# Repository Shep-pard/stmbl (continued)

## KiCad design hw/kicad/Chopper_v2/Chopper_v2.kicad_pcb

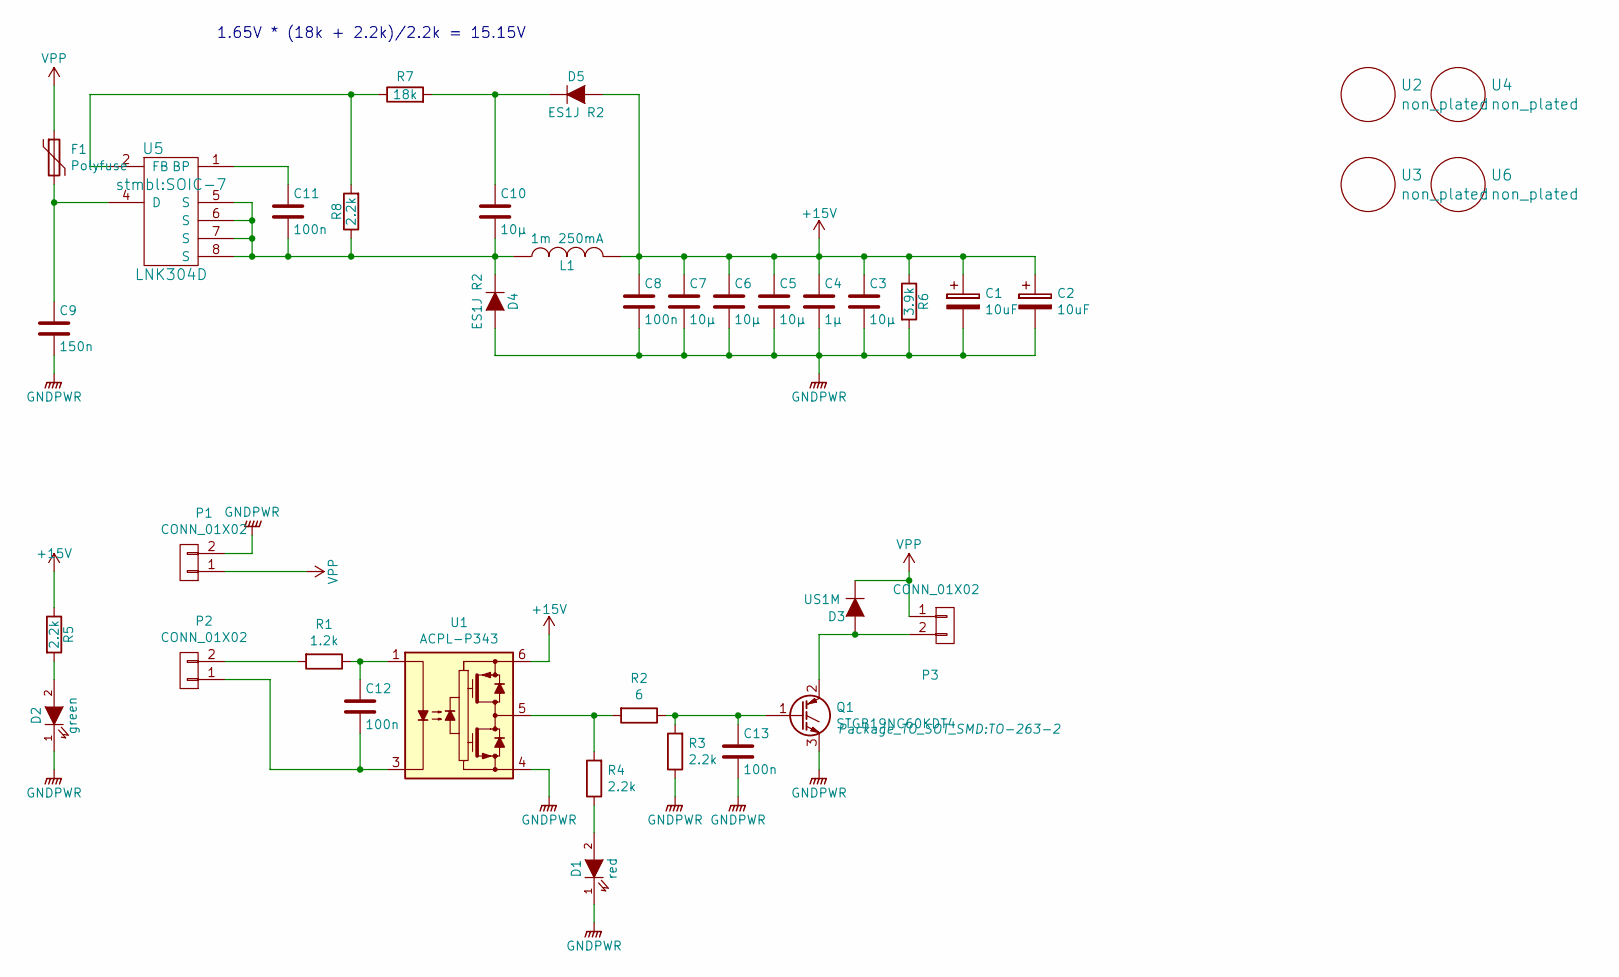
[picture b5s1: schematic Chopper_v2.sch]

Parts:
C1, C2: 10uF; CP_EIA-3216-18_Kemet-A_Pad1.58x1.35mm_HandSolder
C3, C5, C6, C7, C10: 10µ; C_0805; Voltage 25V; Tolerance X5R
C4: 1µ; C_0805; Voltage 25V; Tolerance X5R
C8, C11: 100n; C_0603; Voltage 50V; Tolerance X5R
C9: 150n; C_1808; Voltage 500V; Tolerance X7R
C12, C13: 100n; C_0805; Voltage 25V; Tolerance X5R
D1: red; LED_0805_2012Metric_Castellated
D2: green; LED_0805_2012Metric_Castellated
D3: US1M; D_SMB
D4, D5: ES1J R2; SMA_Standard
F1: Polyfuse; R_0805
L1: 1m 250mA; NPI31W
P1, P3: CONN_01X02; RM5.08_1x2
P2: CONN_01X02; RM3.5_1x2
Q1: STGB19NC60KDT4; TO-263-2
R1: 1.2k; R_0805
R2: 6; R_2512
R3, R4: 2.2k; R_0805
R5, R8: 2.2k; R_0805; Tolerance 1%
R6: 3.9k; R_0805; Tolerance 1%
R7: 18k; R_0805; Tolerance 1%
U1: ACPL-P343; SSO-6_6.8x4.6mm_P1.27mm_Clearance7mm
U2, U3, U4, U6: non_plated; non_plated_3mm
U5: LNK304D; SOIC-7

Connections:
+15V: C1.1, C2.1, C3.1, C4.1, C5.1, C6.1, C7.1, C8.1, D5.2 (A), L1.2, R5.1, R6.1, U1.6 (VCC)
GNDPWR: C1.2, C2.2, C3.2, C4.2, C5.2, C6.2, C7.2, C8.2, C9.2, C13.2, D1.1 (K), D2.1 (K), D4.2 (A), P1.2, Q1.3 (E), R3.1, R6.2, U1.4 (VEE)
unnamed: C9.1, F1.2, U5.4 (D)
unnamed: C10.1, D5.1 (K), R7.2
unnamed: C10.2, C11.2, D4.1 (K), L1.1, R8.1, U5.5 (S), U5.6 (S), U5.7 (S), U5.8 (S)
unnamed: C11.1, U5.1 (BP)
unnamed: C12.1, R1.1, U1.1 (A)
unnamed: C12.2, P2.1, U1.3 (C)
unnamed: C13.1, Q1.1 (G), R2.1, R3.2
unnamed: D1.2 (A), R4.1
unnamed: D2.2 (A), R5.2
unnamed: D3.2 (A), P3.2, Q1.2 (C)
unnamed: P2.2, R1.2
unnamed: R2.2, R4.2, U1.5 (VO)
unnamed: R7.1, R8.2, U5.2 (FB)
VPP: D3.1 (K), F1.1, P1.1, P3.1

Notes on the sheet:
1.65V * (18k + 2.2k)/2.2k = 15.15V

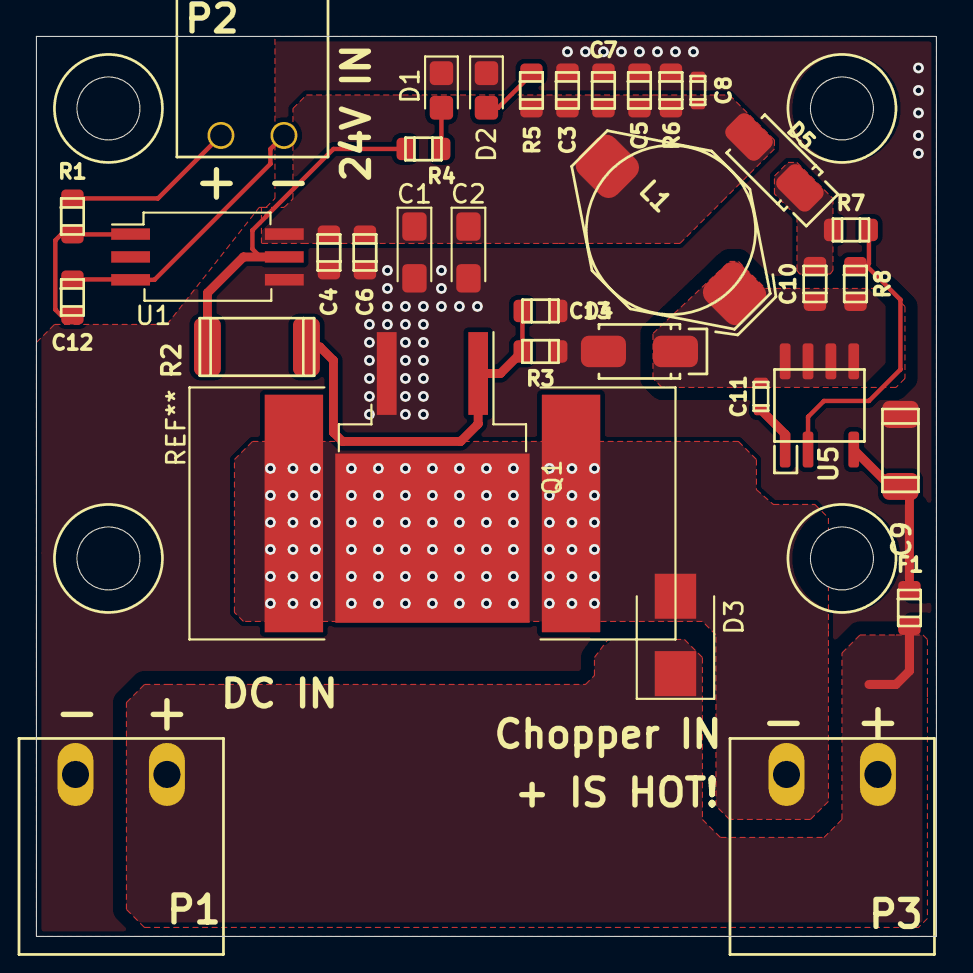
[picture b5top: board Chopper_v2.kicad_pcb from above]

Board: 2 copper layers, 50.0 x 50.0 mm, 38 parts (0 on the bottom side), 16 nets.

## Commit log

2020-04-04 added HW files
2020-05-18 added IKCM30F60GD
2020-05-18 schematic update
2020-05-30 changes for IKCM30F60GD
2020-10-20 some kicad changes
